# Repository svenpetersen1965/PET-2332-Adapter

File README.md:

# PET-2332-Adapter
An EPROM adapter for the 2332 sockets in the Commodore (dynamic) PET and 40xx/80xx.

# Compatibility
* CBM80xx: The adapter is compatible with all ROM sockets (UD6-UD12), except the Character ROM (UA3).
* CBM40xx: The adapter is compatible with all ROM sockets (UD6-UD12), except the Character ROM (UA3).

The CBM30xx are PET2001N-16 or -32 (label in the back).

* PET2001N: The adapter is compatible with all 4k ROM sockets (UD3-UD7 & UD9), <b>except</b> the Edit ROM (UD8) and the Character ROM (UF10). 

This adapter is <b>not suitable</b> for the character generator ROM in any machine (neither C64, nor VIC-20).

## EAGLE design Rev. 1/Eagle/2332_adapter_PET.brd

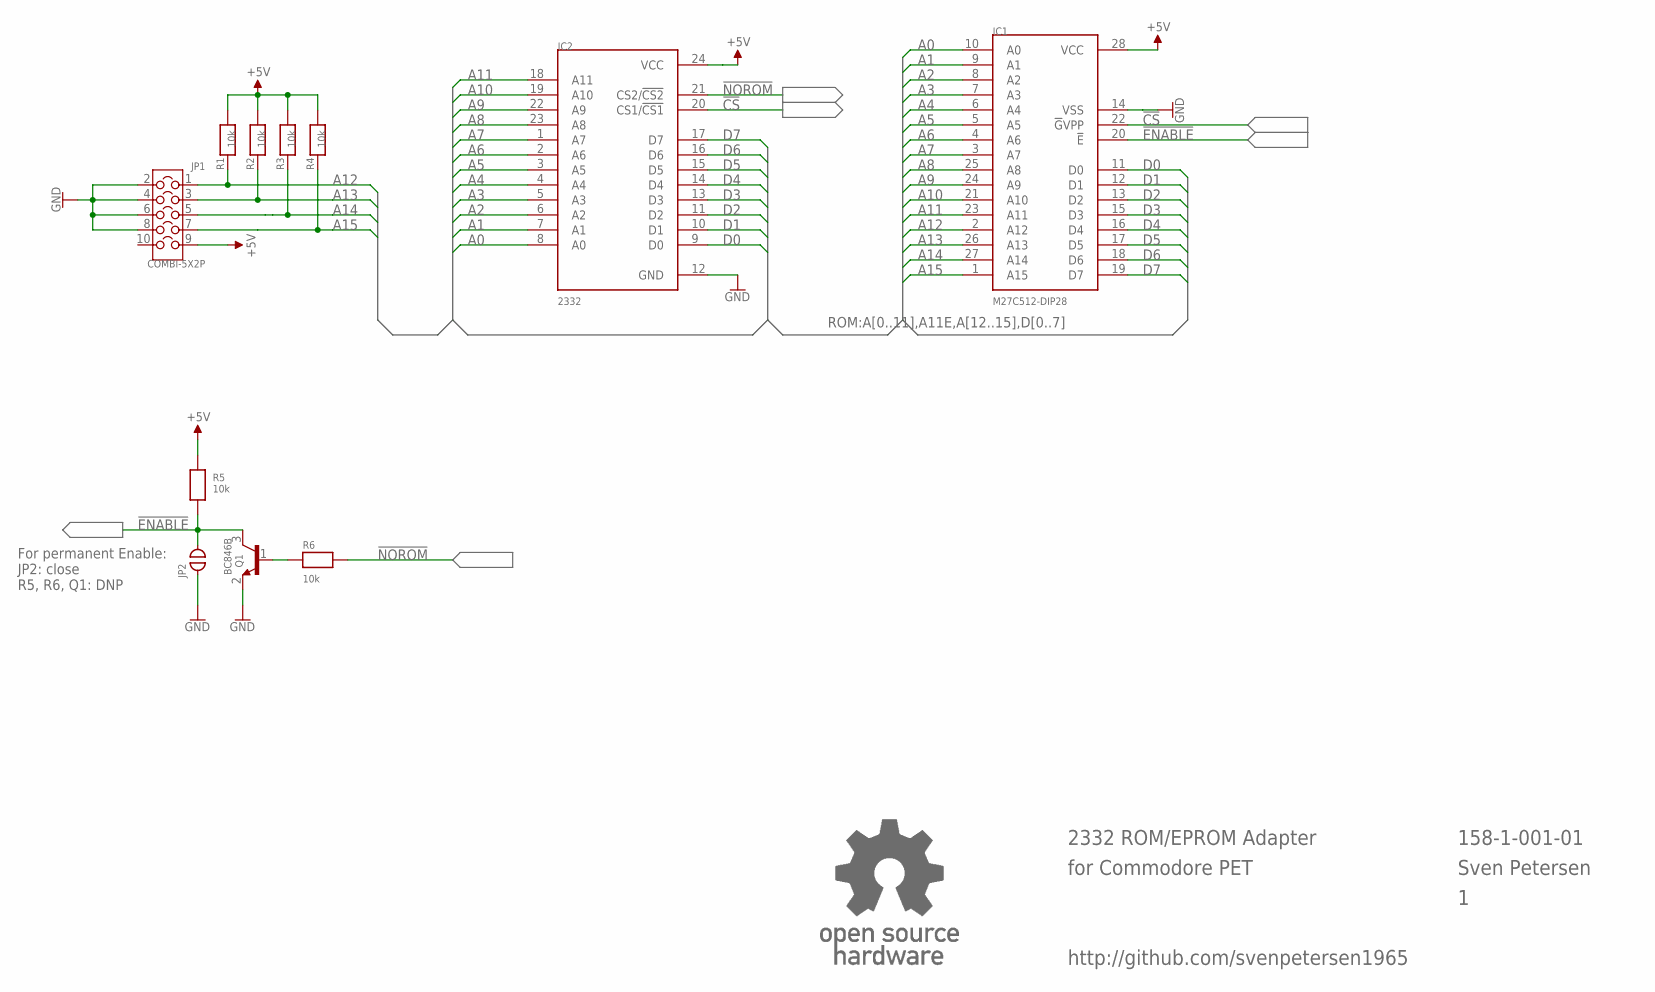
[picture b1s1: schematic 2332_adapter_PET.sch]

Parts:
IC1: M27C512-DIP28; DIL28-6
IC2: 2332; DIL24_SOCKET
JP1: COMBI-5X2P; COMBI-5X2
JP2: OPEN; CP_OP
Q1: BC846B; SOT23
R1, R2, R3, R4, R5, R6: 10k; 0805
U$6: OPEN_SOURCE_HW; OPENHW

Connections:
!CS: IC1.22 (!G!VPP), IC2.20 (CS1/!CS1)
!ENABLE: IC1.20 (!E), JP2.2, Q1.3 (C), R5.1
!NOROM: IC2.21 (CS2/!CS2), R6.2
+5V: IC1.28 (VCC), IC2.24 (VCC), JP1.9, R1.2, R2.2, R3.2, R4.2, R5.2
A0: IC1.10 (A0), IC2.8 (A0)
A1: IC1.9 (A1), IC2.7 (A1)
A2: IC1.8 (A2), IC2.6 (A2)
A3: IC1.7 (A3), IC2.5 (A3)
A4: IC1.6 (A4), IC2.4 (A4)
A5: IC1.5 (A5), IC2.3 (A5)
A6: IC1.4 (A6), IC2.2 (A6)
A7: IC1.3 (A7), IC2.1 (A7)
A8: IC1.25 (A8), IC2.23 (A8)
A9: IC1.24 (A9), IC2.22 (A9)
A10: IC1.21 (A10), IC2.19 (A10)
A11: IC1.23 (A11), IC2.18 (A11)
A12: IC1.2 (A12), JP1.1, R1.1
A13: IC1.26 (A13), JP1.3, R2.1
A14: IC1.27 (A14), JP1.5, R3.1
A15: IC1.1 (A15), JP1.7, R4.1
D0: IC1.11 (D0), IC2.9 (D0)
D1: IC1.12 (D1), IC2.10 (D1)
D2: IC1.13 (D2), IC2.11 (D2)
D3: IC1.15 (D3), IC2.13 (D3)
D4: IC1.16 (D4), IC2.14 (D4)
D5: IC1.17 (D5), IC2.15 (D5)
D6: IC1.18 (D6), IC2.16 (D6)
D7: IC1.19 (D7), IC2.17 (D7)
GND: IC1.14 (VSS), IC2.12 (GND), JP1.2, JP1.4, JP1.6, JP1.8, JP2.1, Q1.2 (E)
unnamed: Q1.1 (B), R6.1

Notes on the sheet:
158-1-001-01
Sven Petersen
http://github.com/svenpetersen1965
For permanent Enable: JP2: close R5, R6, Q1: DNP
2332 ROM/EPROM Adapter
for Commodore PET

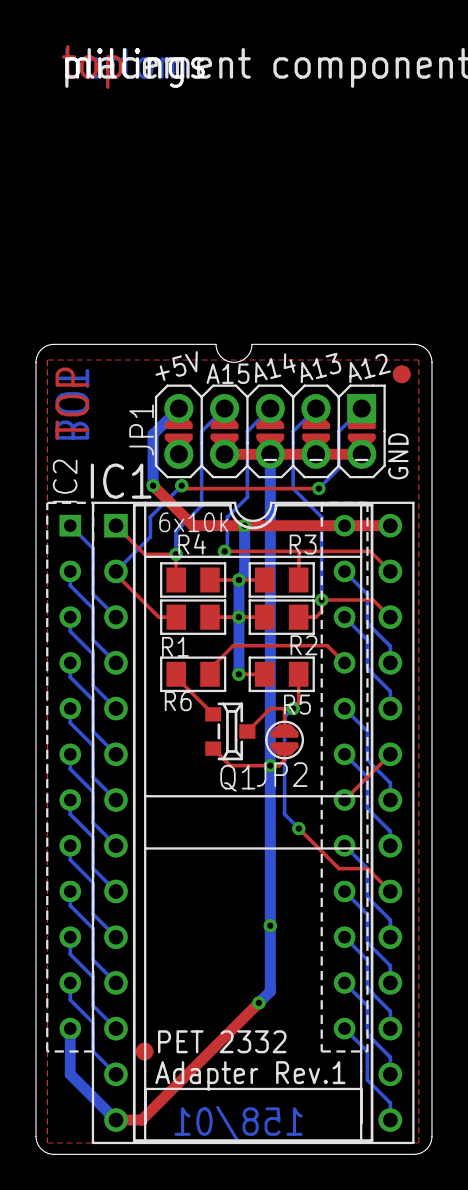
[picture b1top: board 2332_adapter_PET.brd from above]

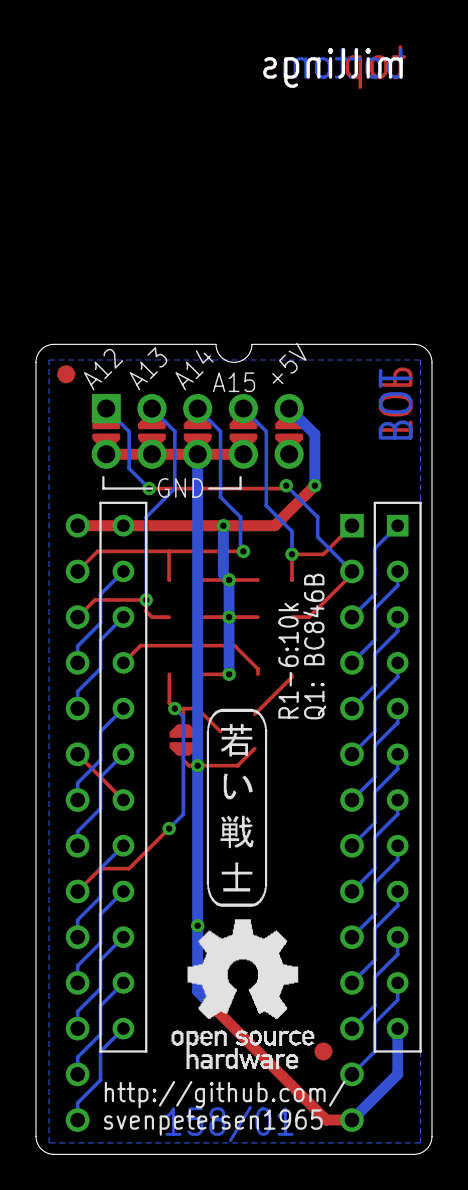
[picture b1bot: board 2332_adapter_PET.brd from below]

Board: 2 copper layers, 22.0 x 45.0 mm, 18 parts (2 on the bottom side), 30 nets.

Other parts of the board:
U$11: SVEN_TAG
U$16: GS28P
U$17, U$18: SMD_REF_R1MM
U$19: 2LAYER
U$20: PCB-TITLE/

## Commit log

2022-04-23 Initial release
